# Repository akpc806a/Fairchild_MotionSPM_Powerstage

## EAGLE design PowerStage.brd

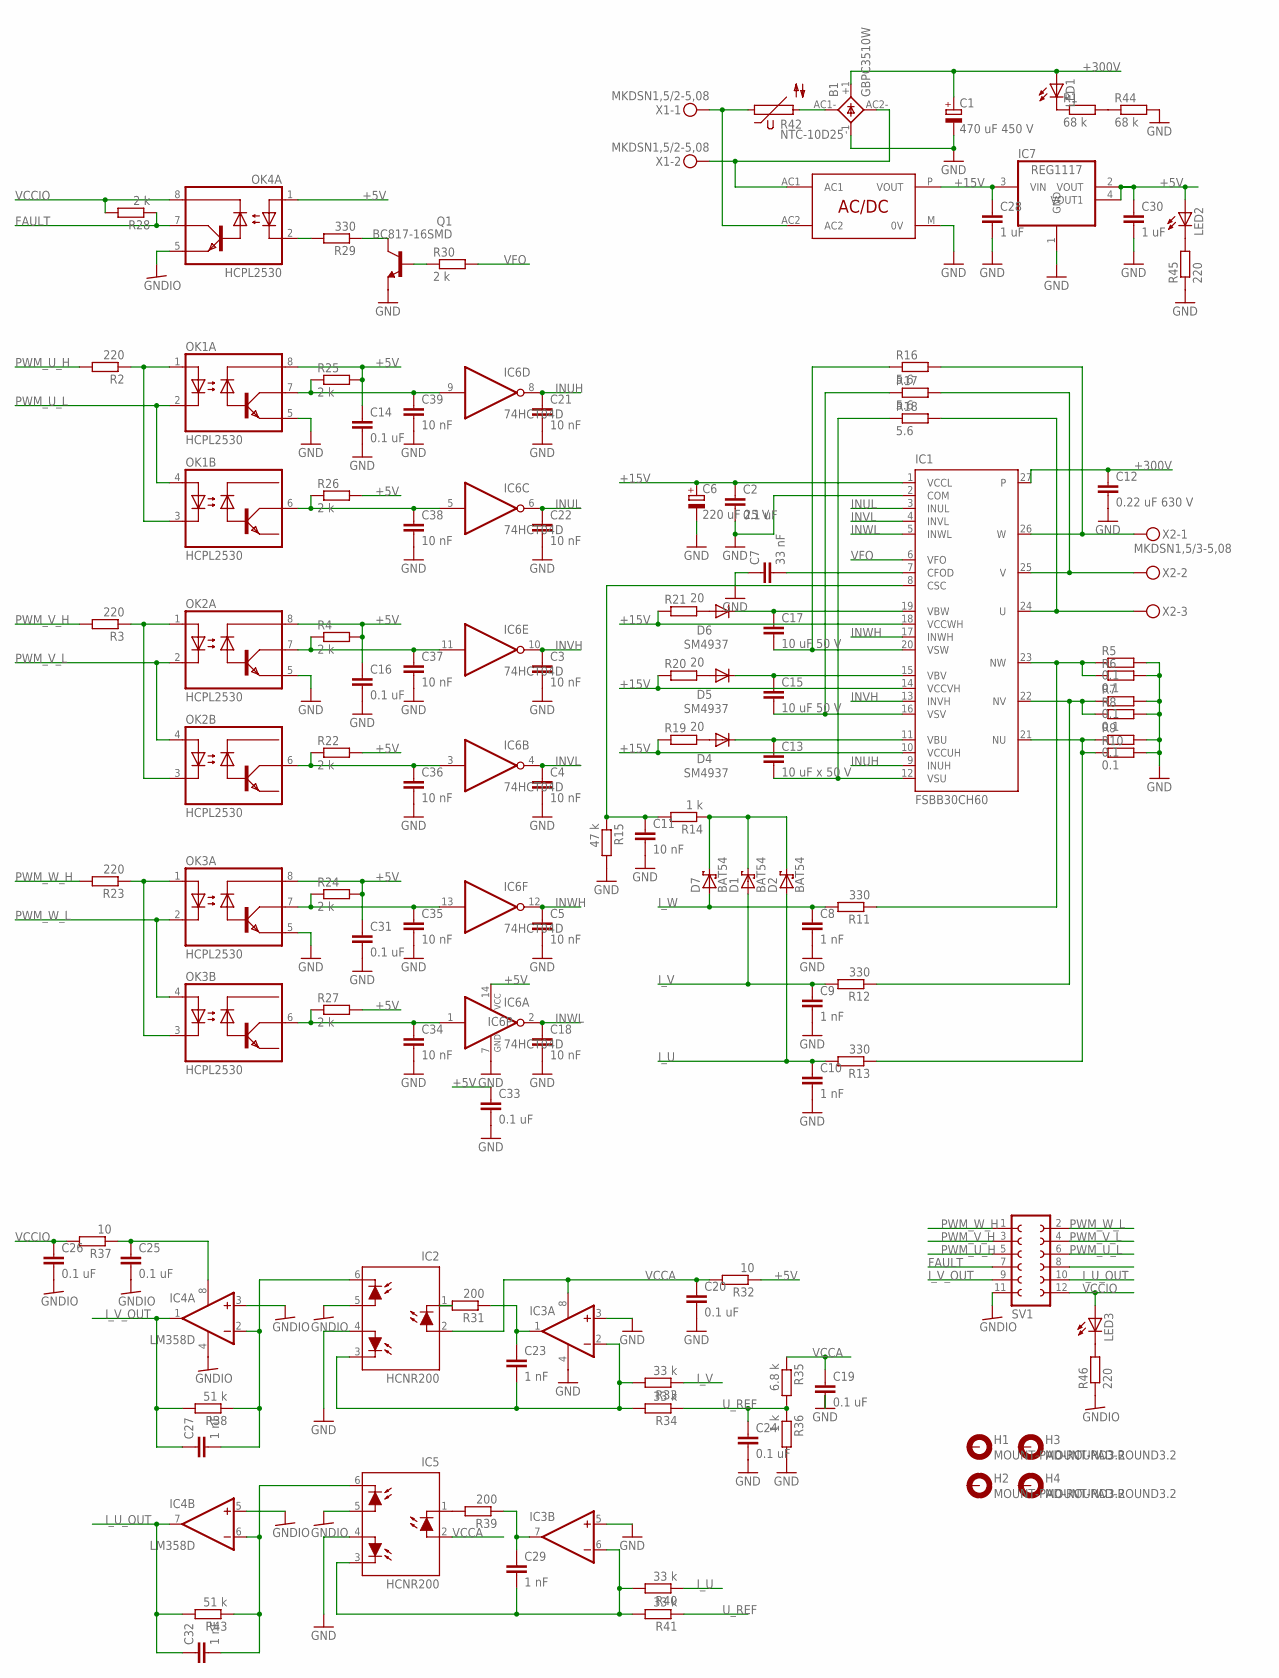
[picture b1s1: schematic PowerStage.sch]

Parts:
B1: GBPC3510W; GBPC-W
C1: 470 uF 450 V; EB35D
C2, C14, C16, C19, C20, C24, C25, C26, C31, C33: 0.1 uF; C0603
C3, C4, C5, C11, C18, C21, C22, C34, C35, C36, C37, C38, C39: 10 nF; C0603
C6: 220 uF 25 V; PANASONIC_G
C7: 33 nF; C0603
C8, C9, C10, C23, C27, C29, C32: 1 nF; C0603
C12: 0.22 uF 630 V; C150-091X182
C13: 10 uF x 50 V; C1210
C15, C17: 10 uF 50 V; C1210
C28, C30: 1 uF; C0603
D1, D2, D7: BAT54; SOT23
D4, D5, D6: SM4937; MELF-MLL41
H1, H2, H3, H4: MOUNT-PAD-ROUND3.2; 3,2-PAD
IC1: FSBB30CH60
IC2, IC5: HCNR200; DIL08-400
IC3: 2AMP_P8+4D; SO08
IC4: LM358D; SO08
IC6: 74HCT04D; SO14
IC7: REG1117; SOT223
LED1, LED2, LED3: LEDCHIP-LED0603; CHIP-LED0603
OK1, OK2, OK3, OK4: HCPL2530; DIL08
Q1: BC817-16SMD; SOT23-BEC
R1, R44: 68 k; R1206
R2, R3, R23, R45, R46: 220; R0603
R4, R22, R24, R25, R26, R27, R28, R30: 2 k; R0603
R5, R6, R7, R8, R9, R10: 0.1; R2512
R11, R12, R13, R29: 330; R0603
R14, R36: 1 k; R0603
R15: 47 k; R0603
R16, R17, R18: 5.6; R1206
R19, R20, R21: 20; R1206
R31, R39: 200; R0603
R32, R37: 10; R0603
R33, R34, R40, R41: 33 k; R0603
R35: 6.8 k; R0603
R38, R43: 51 k; R0603
R42: NTC-10D25; S20K40
SV1: FE06-2
U$1: KUUKO_090873
X1: MKDSN1,5/2-5,08
X2: MKDSN1,5/3-5,08

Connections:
+5V: C14.1, C16.1, C30.1, C31.1, C33.1, IC6.14 (VCC), IC7.2 (VOUT), IC7.4 (VOUT1), LED2.A, OK1.8 (VCC), OK2.8 (VCC), OK3.8 (VCC), OK4.1 (A1), R4.2, R22.2, R24.2, R25.2, R26.2, R27.2, R32.1
+15V: C2.1, C6.+, C28.1, IC1.1 (VCCL), IC1.10 (VCCUH), IC1.14 (VCCVH), IC1.18 (VCCWH), IC7.3 (VIN), R19.1, R20.1, R21.1, U$1.P (VOUT)
+300V: B1.+1 (+), C1.+, C12.1, IC1.27, LED1.A
FAULT: OK4.7 (VO1), R28.1, SV1.7
GND: B1.-1 (-), C1.-, C2.2, C3.2, C4.2, C5.2, C6.-, C7.1, C8.2, C9.2, C10.2, C11.2, C12.2, C14.2, C16.2, C18.2, C19.2, C20.2, C21.2, C22.2, C24.2, C28.2, C30.2, C31.2, C33.2, C34.2, C35.2, C36.2, C37.2, C38.2, C39.2, IC1.2 (COM), IC2.4 (A1), IC3.3 (+IN), IC3.4 (V-), IC3.5 (+IN), IC5.4 (A1), IC6.7 (GND), IC7.1 (GND), OK1.5 (GND), OK2.5 (GND), OK3.5 (GND), Q1.E, R5.2, R6.2, R7.2, R8.2, R9.2, R10.2, R15.2, R36.2, R44.2, R45.1, U$1.M (0V)
GNDIO: C25.2, C26.2, IC2.5 (A2), IC4.3 (+IN), IC4.4 (V-), IC4.5 (+IN), IC5.5 (A2), OK4.5 (GND), R46.1, SV1.11
INUH: C21.1, IC1.9 (INUH), IC6.8 (O)
INUL: C22.1, IC1.3 (INUL), IC6.6 (O)
INVH: C3.1, IC1.13 (INVH), IC6.10 (O)
INVL: C4.1, IC1.4 (INVL), IC6.4 (O)
INWH: C5.1, IC1.17 (INWH), IC6.12 (O)
INWL: C18.1, IC1.5 (INWL), IC6.2 (O)
I_U: C10.1, D2.1 (A), R13.2, R40.1
I_U_OUT: C32.1, IC4.7 (OUT), R43.2, SV1.10
I_V: C9.1, D1.1 (A), R12.2, R33.1
I_V_OUT: C27.1, IC4.1 (OUT), R38.2, SV1.9
I_W: C8.1, D7.1 (A), R11.2
unnamed: IC1.23 (NW), R5.1, R6.1, R11.1
unnamed: OK1.1 (A1), OK1.3 (C2), R2.1
unnamed: B1.AC1- (AC1), R42.2
unnamed: B1.AC2- (AC2), U$1.AC1, X1.2
unnamed: IC1.26 (W), R16.2, X2.1
unnamed: IC1.25 (V), R17.2, X2.2
unnamed: IC1.24 (U), R18.2, X2.3
unnamed: IC5.1 (C), R39.2
unnamed: C25.1, IC4.8 (V+), R37.1
unnamed: IC1.22 (NV), R7.1, R8.1, R12.1
unnamed: IC1.21 (NU), R9.1, R10.1, R13.1
unnamed: C7.2, IC1.7 (CFOD)
unnamed: D1.3 (C), D2.3 (C), D7.3 (C), R14.1
unnamed: C11.1, IC1.8 (CSC), R14.2, R15.1
unnamed: C13.1, D4.C, IC1.11 (VBU)
unnamed: C13.2, IC1.12 (VSU), R18.1
unnamed: D4.A, R19.2
unnamed: C15.1, D5.C, IC1.15 (VBV)
unnamed: C15.2, IC1.16 (VSV), R17.1
unnamed: D5.A, R20.2
unnamed: C17.1, D6.C, IC1.19 (VBW)
unnamed: C17.2, IC1.20 (VSW), R16.1
unnamed: D6.A, R21.2
unnamed: OK4.2 (C1), R29.2
unnamed: Q1.C, R29.1
unnamed: Q1.B, R30.1
unnamed: C23.2, IC2.3 (C1), IC3.2 (-IN), R33.2, R34.2
unnamed: OK2.1 (A1), OK2.3 (C2), R3.1
unnamed: C27.2, IC2.6 (C2), IC4.2 (-IN), R38.1
unnamed: OK3.1 (A1), OK3.3 (C2), R23.1
unnamed: C39.1, IC6.9 (I), OK1.7 (VO1), R25.1
unnamed: C29.2, IC3.6 (-IN), IC5.3 (C1), R40.2, R41.2
unnamed: C29.1, IC3.7 (OUT), R39.1
unnamed: C23.1, IC3.1 (OUT), R31.1
unnamed: C32.2, IC4.6 (-IN), IC5.6 (C2), R43.1
unnamed: IC2.1 (C), R31.2
unnamed: C38.1, IC6.5 (I), OK1.6 (VO2), R26.1
unnamed: C37.1, IC6.11 (I), OK2.7 (VO1), R4.1
unnamed: C36.1, IC6.3 (I), OK2.6 (VO2), R22.1
unnamed: C35.1, IC6.13 (I), OK3.7 (VO1), R24.1
unnamed: C34.1, IC6.1 (I), OK3.6 (VO2), R27.1
unnamed: LED1.C, R1.1
unnamed: R1.2, R44.1
unnamed: LED2.C, R45.2
unnamed: LED3.C, R46.2
unnamed: R42.1, U$1.AC2, X1.1
PWM_U_H: R2.2, SV1.5
PWM_U_L: OK1.2 (C1), OK1.4 (A2), SV1.6
PWM_V_H: R3.2, SV1.3
PWM_V_L: OK2.2 (C1), OK2.4 (A2), SV1.4
PWM_W_H: R23.2, SV1.1
PWM_W_L: OK3.2 (C1), OK3.4 (A2), SV1.2
U_REF: C24.1, R34.1, R35.2, R36.1, R41.1
VCCA: C19.1, C20.1, IC2.2 (A), IC3.8 (V+), IC5.2 (A), R32.2, R35.1
VCCIO: C26.1, LED3.A, OK4.8 (VCC), R28.2, R37.2, SV1.12
VFO: IC1.6 (VFO), R30.2

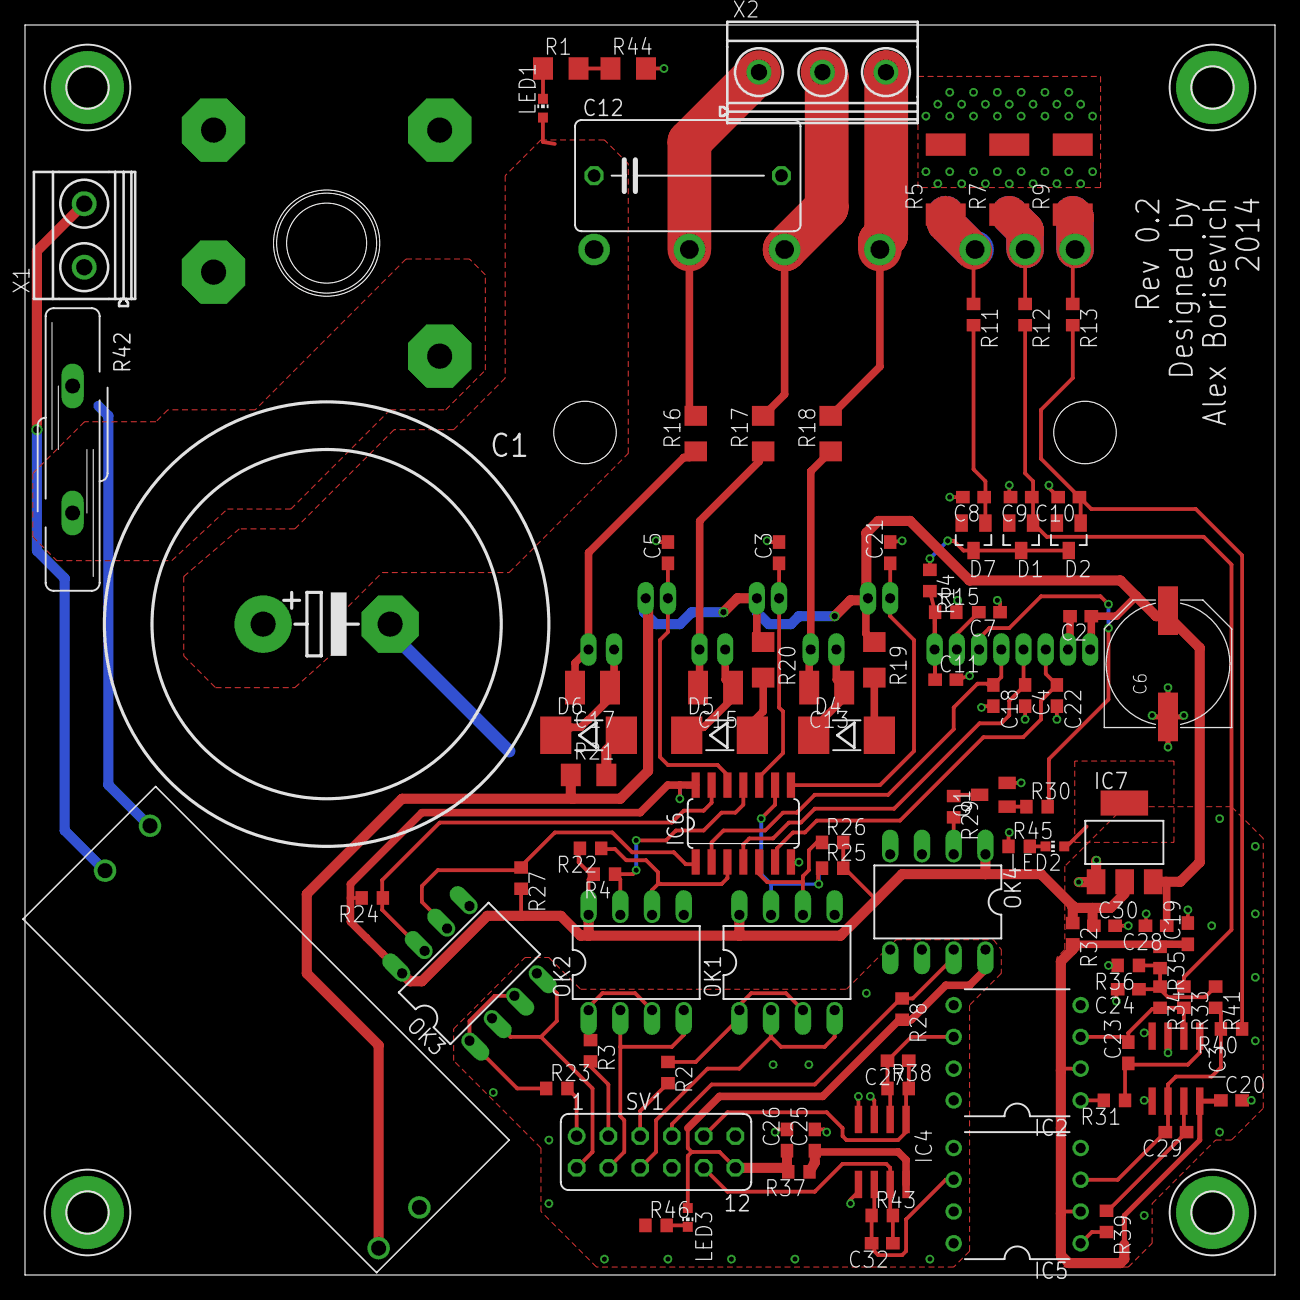
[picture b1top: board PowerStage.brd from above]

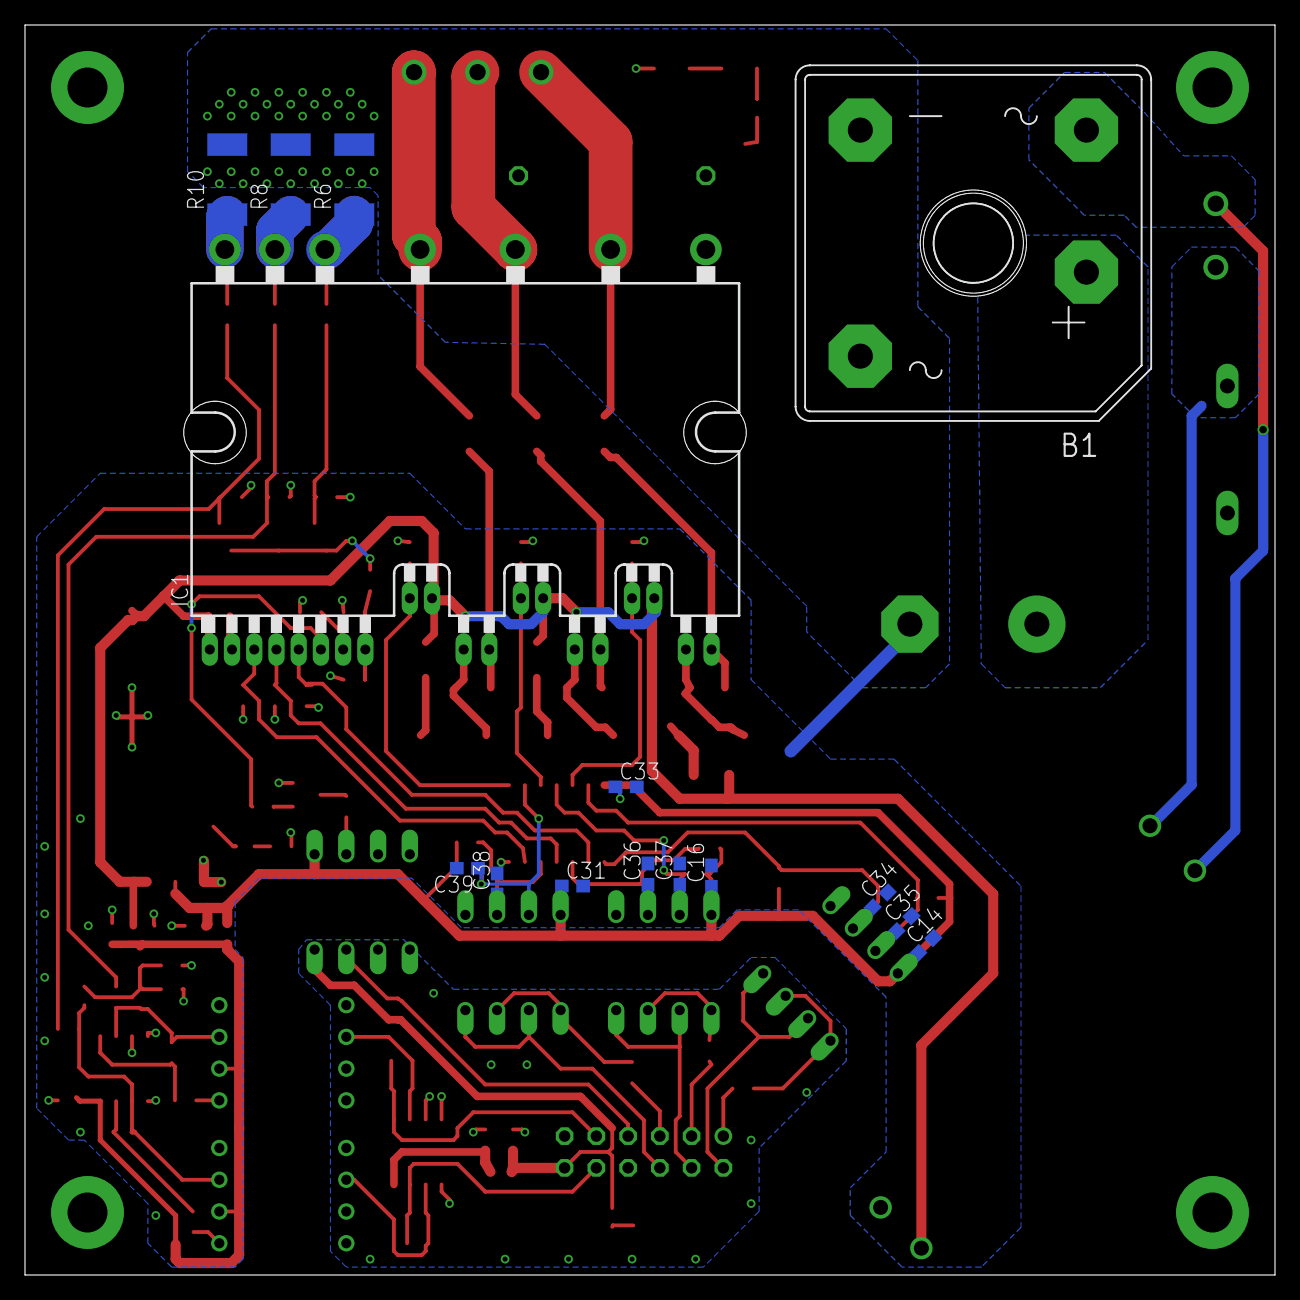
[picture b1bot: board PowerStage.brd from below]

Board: 2 copper layers, 100.0 x 100.0 mm, 115 parts (15 on the bottom side), 73 nets.

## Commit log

2014-09-14 :neckbeard: Added .gitattributes & .gitignore files
2014-09-14 Initial version
    IGBT module tested at low voltage
2015-01-15 Stable version
    Tested at 1 kW motor
